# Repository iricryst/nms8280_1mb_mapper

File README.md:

# nms8280_1mb_mapper

Project to document and create a 1MB module for a Philips NMS8280 MSX. Based on a paper by Hans Oranje.

This project is far from production ready. It is only a concept. I wouldn't even call it a proof of concept. 

## Reference documents

- [1MB PC SIMM by Hans Oranje](./1mbnms8280e.pdf)
- [Philips NMS 8280 Service Manual](./Philips%20NMS%208280%20Service%20Manual.pdf)

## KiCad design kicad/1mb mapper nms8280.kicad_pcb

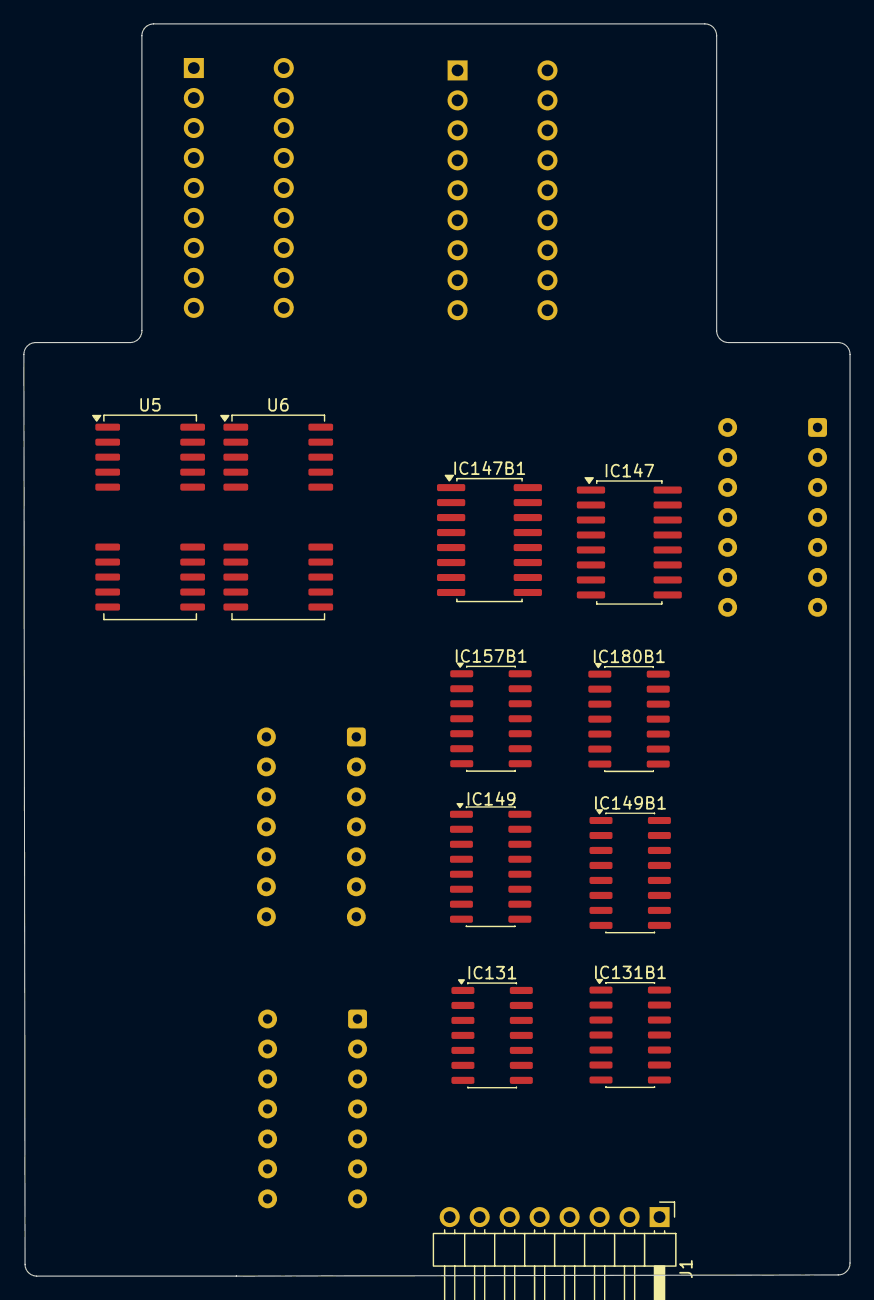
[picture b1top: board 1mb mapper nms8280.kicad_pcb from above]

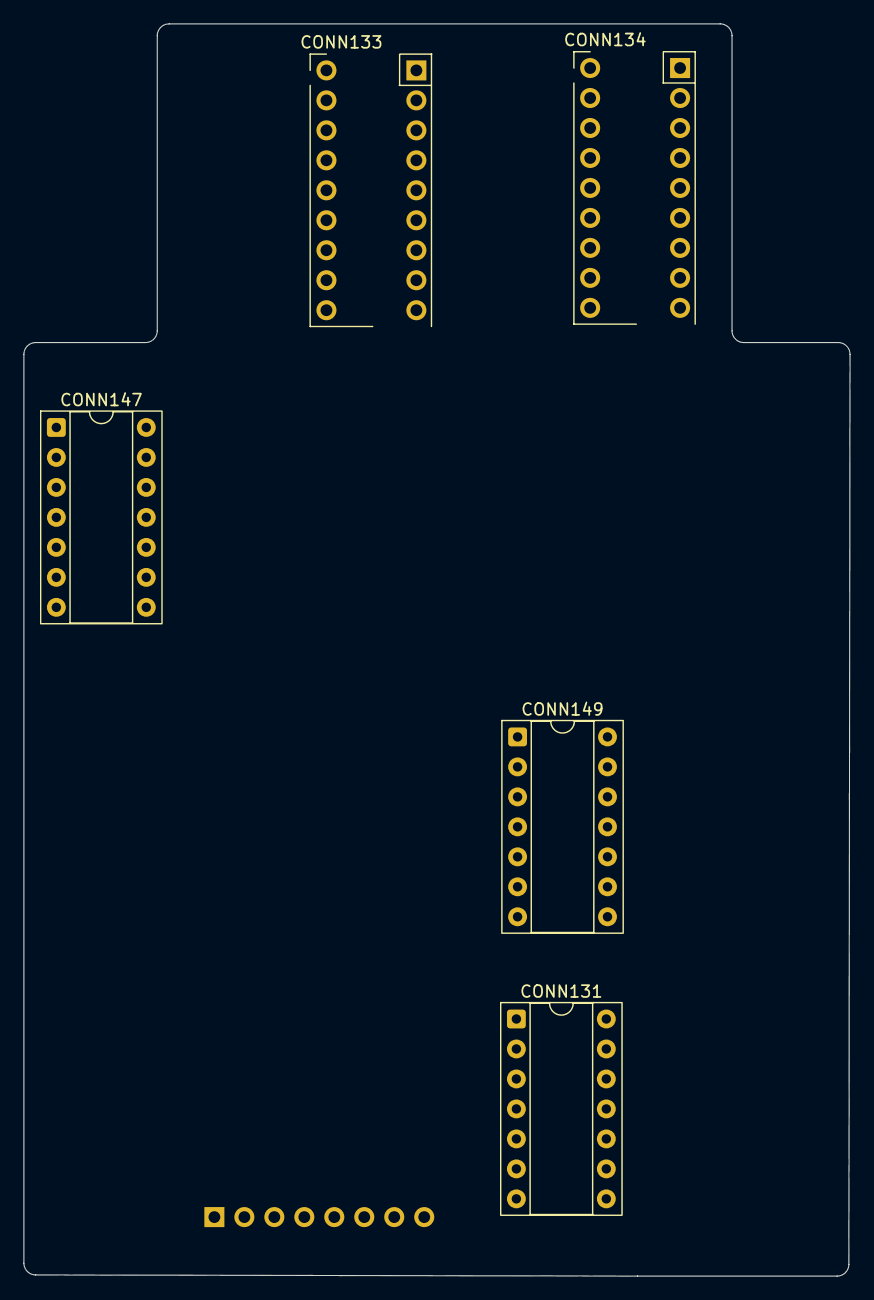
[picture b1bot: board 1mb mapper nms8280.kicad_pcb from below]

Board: 2 copper layers, 70.0 x 106.1 mm, 16 parts (5 on the bottom side), 70 nets, no tracks yet.

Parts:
CONN131, CONN147, CONN149: DIP-14_W7.62mm_Socket
CONN133, CONN134: PinHeader_2x09_P2.54mm_Vertical
IC131, IC131B1, IC157B1, IC180B1: SOIC-14_3.9x8.7mm_P1.27mm
IC147, IC147B1: 74LS157; SOIC-16W_5.3x10.2mm_P1.27mm
IC149, IC149B1: 74LS670; SOIC-16_3.9x9.9mm_P1.27mm
J1: Conn_01x08_Pin; PinHeader_1x08_P2.54mm_Horizontal
U5, U6: SOJ-26_7.62x18.415mm_P1.27mm

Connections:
/buffer cas section/<NO NET>: IC180B1.1 (1A), IC180B1.2 (1B), J1.1
/buffer cas section/GND: CONN131.7 (GND), CONN147.8 (GND), CONN149.8 (GND), IC131.7 (GND), IC131B1.7 (GND), IC147.8 (GND), IC147B1.8 (GND), IC149.8 (GND), IC149B1.2 (D3), IC149B1.3 (D4), IC149B1.8 (GND), IC157B1.7 (GND), IC180B1.7 (GND)
/buffer cas section/IC131_P1_IC131B: CONN131.1 (1A), IC131.1 (1E), IC131B1.1 (1E), IC131B1.13 (4E)
/buffer cas section/IC131_P2: CONN131.2 (1B), IC131.2 (1D)
/buffer cas section/IC131_P3: CONN131.3 (1Y), IC131.3 (1O)
/buffer cas section/IC131_P4_IC131B: CONN131.4 (2A), IC131.4 (2E), IC131B1.4 (2E)
/buffer cas section/IC131_P5: CONN131.5 (2B), IC131.5 (2D)
/buffer cas section/IC131_P6: CONN131.6 (2Y), IC131.6 (2O)
/buffer cas section/IC131_P8: CONN131.8 (3Y), IC131.8 (3O)
/buffer cas section/IC131_P9: CONN131.9 (3A), IC131.9 (3D)
/buffer cas section/IC131_P10_IC131B: CONN131.10 (3B), IC131.10 (3E), IC131B1.10 (3E)
/buffer cas section/IC131_P11: CONN131.11 (4Y), IC131.11 (4O)
/buffer cas section/IC131_P12: CONN131.12 (4A), IC131.12 (4D)
/buffer cas section/IC131_P13: CONN131.13 (4B), IC131.13 (4E)
/buffer cas section/IC147_P1_IC147B: CONN147.1 (S), IC147.1 (S), IC147B1.1 (S)
/buffer cas section/IC147_P2: CONN147.2 (A0), IC147.2 (I0a)
/buffer cas section/IC147_P3: CONN147.3 (B0), IC147.3 (I1a)
/buffer cas section/IC147_P4: CONN147.4 (Y0), IC147.4 (Za)
/buffer cas section/IC147_P5: CONN147.5 (A1), IC147.5 (I0b)
/buffer cas section/IC147_P6: CONN147.6 (B1), IC147.6 (I1b)
/buffer cas section/IC147_P7: CONN147.7 (Y1), IC147.7 (Zb)
/buffer cas section/IC147_P9: CONN147.9 (Y2), IC147.9 (Zc)
/buffer cas section/IC147_P10: CONN147.10 (B2), IC147.10 (I1c)
/buffer cas section/IC147_P11: CONN147.11 (A2), IC147.11 (I0c)
/buffer cas section/IC147_P12: CONN147.12 (Y3), IC147.12 (Zd)
/buffer cas section/IC147_P13: CONN147.13 (B3), IC147.13 (I1d)
/buffer cas section/IC147_P14: CONN147.14 (A3), IC147.14 (I0d)
/buffer cas section/IC147_P15_IC147B: IC147.15 (E), IC147B1.15 (E)
/buffer cas section/IC149_P1: CONN149.1 (D2), IC149.1 (D2)
/buffer cas section/IC149_P2: CONN149.2 (D3), IC149.2 (D3)
/buffer cas section/IC149_P3: CONN149.3 (D4), IC131B1.3 (1O), IC149.3 (D4), J1.4
/buffer cas section/IC149_P4_IC149B: CONN149.4 (RB), IC149.4 (Rb), IC149B1.4 (Rb)
/buffer cas section/IC149_P5_IC149B: CONN149.5 (RA), IC149.5 (Ra), IC149B1.5 (Ra)
/buffer cas section/IC149_P6: CONN149.6 (Q4), IC131B1.2 (1D), IC147B1.3 (I1a), IC149.6 (Q4)
/buffer cas section/IC149_P7: CONN149.7 (Q3), IC147B1.2 (I0a), IC149.7 (Q3)
/buffer cas section/IC149_P9: CONN149.9 (Q2), IC149.9 (Q2)
/buffer cas section/IC149_P10: CONN149.10 (Q1), IC149.10 (Q1)
/buffer cas section/IC149_P11_IC149B: CONN149.11 (ER), IC149.11 (~Er), IC149B1.11 (~Er)
/buffer cas section/IC149_P12_IC149B: CONN149.12 (EW), IC149.12 (~Ew), IC149B1.12 (~Ew)
/buffer cas section/IC149_P13_IC149B: CONN149.13 (WB), IC149.13 (Wb), IC149B1.13 (Wb)
/buffer cas section/IC149_P14_IC149B: CONN149.14 (WA), IC149.14 (Wa), IC149B1.14 (Wa)
/buffer cas section/Vcc: CONN131.14 (Vcc), IC131.14 (Vcc), IC131B1.14 (Vcc), IC147.16 (VCC), IC147B1.16 (VCC), IC149.16 (VCC), IC149B1.16 (VCC), IC157B1.12 (4A), IC157B1.13 (4B), IC157B1.14 (Vcc), IC180B1.12 (4A), IC180B1.13 (4B), IC180B1.14 (Vcc)
/ram section/A0_IC133/134_P14: U5.9 (A0), U6.9 (A0)
/ram section/A1_IC133/134_P13: U5.10 (A1), U6.10 (A1)
/ram section/A2_IC133/134_P12: U5.11 (A2), U6.11 (A2)
/ram section/A3_IC133/134_P11: U5.12 (A3), U6.12 (A3)
/ram section/A4_IC133/134_P8: U5.14 (A4), U6.14 (A4)
/ram section/A5_IC133/134_P7: U5.15 (A5), U6.15 (A5)
/ram section/A6_IC133/134_P6: U5.16 (A6), U6.16 (A6)
/ram section/A7_IC133/134_P10: U5.17 (A7), U6.17 (A7)
/ram section/CAS_IC133/134_P16: U5.23 (CAS), U6.23 (CAS)
/ram section/GND: CONN133.18 (GND_18), CONN134.18 (GND_18), U5.22 (OE), U5.26 (GND), U6.22 (OE), U6.26 (GND)
/ram section/RAS_IC133_P5: U5.4 (RAS), U6.4 (RAS)
/ram section/WE_IC133_P4: U5.3 (WE), U6.3 (WE)
A8_IC147B_P4: IC147B1.4 (Za), U5.18 (A8), U6.18 (A8)
A9_IC147B_P7: IC147B1.7 (Zb), U5.5 (A9), U6.5 (A9)
unnamed: IC131B1.5 (2D), IC147B1.5 (I0b), IC149B1.10 (Q1)
unnamed: IC131B1.6 (2O), IC149B1.15 (D1), J1.3
unnamed: IC131B1.9 (3D), IC147B1.6 (I1b), IC149B1.9 (Q2)
unnamed: IC131B1.8 (3O), IC149B1.1 (D2), J1.2
unnamed: IC147B1.9 (Zc), IC147B1.10 (I1c), IC147B1.11 (I0c)
unnamed: IC147B1.12 (Zd), IC147B1.13 (I1d), IC147B1.14 (I0d)
unnamed: IC157B1.1 (1A), IC157B1.4 (2A), J1.5
unnamed: IC157B1.2 (1B), IC157B1.5 (2B), IC180B1.6 (2Y)
unnamed: IC157B1.3 (1Y), J1.6
unnamed: IC157B1.6 (2Y), J1.7
unnamed: IC157B1.9 (3A), IC157B1.10 (3B), IC157B1.11 (4Y)
unnamed: IC180B1.3 (1Y), IC180B1.4 (2A)
unnamed: IC180B1.5 (2B), J1.8
unnamed: IC180B1.9 (3A), IC180B1.10 (3B), IC180B1.11 (4Y)
